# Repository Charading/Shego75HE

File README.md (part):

<h1 style="margin-bottom:0;">Shego75HE</h1>
<h4 style="margin-top:0;">Probably the first magnetic keyboard running QMK firmware.</h4>

> 📖 **[Read the latest update →](UPDATE.md)**

### Introduction&nbsp; 

I couldn't find a keyboard with the all of features that I wanted at all, so I resorted to building my own one. After testing a lot of keyboards, I wanted one that had a mix of all different features from multiple keyboards. This project has taken many, many, many months, starting from experimentaion and various mini protypes like the [Shego16](https://github.com/Charading/SHEGO16-QMK-Hall-Effect-Macropad).

### Design and Inspiration 💡
I think the exploded 75% layout is one of the best layouts but sadly it's not as aftermarket as the generic 60% layout so my only options for trying to find a board were scarce. For aesthetics, I went with Shego because my mind was blank and tbh, I just wanted a cool silkscreen too lol. 

I do love the **Ajazz AK820 Pro** and it's clean design, along with the added screen. I do wish it could run QMK/VIA firmware though. Another board I tested was the **GamaKay TK75HEV2** I wanted my board to be quite similar to both, but have everything I've ever wanted. 

Features I wanted

* Hall Sensors
* SOCD
* Rapid Trigger
* Volume Knob
* Ambient Lighting
* Screen
* North-facing RGB
* 75% Layout
* QMK/VIA Compatible
* Works with SignalRGB (per-key not that stupid one-zone nonsense)

#### Firmware 👨‍💻
I originally tried raw C, then riskable put me on Rust, but after creating a successful prototype, I had a revelation. the idea I had is to use normal QMK firmware since I was a little bit familiar with it, then heavily modify my clone of it to work with hall sensors. 

*I am still designing a drop in [module](https://github.com/Charading/qmk-hallscan) that can make anyone be able to use the logic for QMK. Project is ongoing*

Oh yeah, to make my life easier, and save my poor fingers from typing `qmk compile -kb shego75_v1 -km default` a million times, I developed a VS Code extension, a small one-click button that compiles QMK firmware. Find it [here](https://github.com/Charading/QMK-Compile-button-for-VS-Code).

The screen/ESP32 portion is written in C++ inside Arduino IDE.

###### The Sensors 🧲
After doing extensive research and testing with breadboards and Raspberry Pi Pico boards, I settled on using the RP2040 for my base MCU. I was going to use HC4067s, but I didn't really understand multiplexer cascading so after looking for a bit, I stumbled upon the ADG732 so I now use three of these, which means I do not need to use a MCP3208 external ADC *(my god, I recently was trying to get this to work using my sensor-to-matrix logic in QMK but couldn't for the life of me)* and I could use only 3 of the 4 analog pins.

###### How it works 🔎
Essentially, the bread and butter is that the firmware scans across three ADG732 muxes - *which I got really cheap for ~£2 on AliExpress*, and this 'injects' keypresses directly into the key matrix so that it works with VIA and key remapping also. 

On startup, the sensors calibrate with a baseline threshold and when the sensors deviate by a certain % amount, the keypress is registered. I even added hysteresis so I have some kind of rapid trigger.

Debugging keycodes enable printing to QMK Toolbox's HID Console

* `DEBUG_ADC`  - Prints ADC values
* `DEBUG_KEYS` - Prints on keypress events
* `DEBUG_RAW`  - Prints the raw VIA keycode on keypresses, i.e *0x67*

I believe it still prints keys and raw to the screen on a little popup text box too.

###### The Lighting 💡
For the lighting, I ket it simple, and just use SignalRGB,  but in the future I want to maybe add OpenRGB support as well and my own custom lighting section in my Electron app. I have made the [plugin](SignalRGB/SHEGO75.js).

It has full per-key north-facing rgb, a 10-led ambient strip and a 3-led status bar, there is also a 3-pin jst 1.25mm connector footprint in the corner for optional extending *(maybe for a future case, underglow?)*.

The SRGB plugin uses `LedGroups()` to create segments so it has three draggable windows to mess around with.

```javascript
export function LedGroups() {
	return [
		{ name: "Keys",    leds: vKeys },
		{ name: "Ambient", leds: vAmbientKeys },
		{ name: "Status", leds: vStatusKeys }
	];
}
```
 It is designed as one continuous strip though, on `GP17`, but there is a transistor pair on `GP23` which is controlled by the `LED_TOG` custom keycode and cuts power to the LEDs.

 When focused on the screen/layer 3 toggled, the status bar will turn blue.

 When debugging is enabled via `DEBUG_ADC`,`DEBUG_KEYS` or `DEBUG_RAW`, the ambient strip should marque orange.

###### The Screen 📺

Sadly, I couldn't figure out how to get SPI working to talk to the screen for GIF upload and playback via HID, so I approached it a different way.

I built an isolated ESP32 system using [my fork](/esp32_display) of a GIF player repo. I basically redid it to have a little menu and file system, and work a different way to the original. Instead of it automatically copying the GIF to flash and autoplaying, I can browse the SD card, choose which GIF to display, it copies it to SPIFFS, then plays. This way it persists even after power off. 

The screen is [this](https://www.aliexpress.com/item/1005004490846551.html) ST7735/GC9107 8-pin, 0.85", 128x128 IPS display.

To get the QMK firmware to communicate with the ESP32 system, I created custom VIA keycodes which send UART text strings and text commands such as `MENU_OPEN`, `MENU_UP`,`MENU_DOWN` and `MENU_SELECT` allow me to navigate and choose an animation.

4-stage PWM controlled backlight with `TFT_BRIGHTNESS_UP` and `TFT_BRIGHTNESS_DOWN`, via a [AO3401](https://www.aosmd.com/res/data_sheets/AO3401.pdf) transistor. 

I also made a a timer page, settings page, and hardcoded focus toggle which layer 3 + encoder press turns the rotation into menu navigation, and press is the select. 

In a small update, I added a I2C connection between the RP2040 and the ESP32 which I was thinking I could use for GIF passthrough and sending in the future but this is not implemented yet.

##### Firmware Issues
I want a way to use QMK's `raw_hid_receive` and `raw_hid_send` so I can have my own custom software that can change per-key actuation, I could implement DKS, upload GIFs to the SD card/directly to the screen and even manage the card's storage. 

I managed to create a small Electron app that can communicate with the board, but it's still in development.

I realised that SignalRGB consumes packets so I had to edit the `signalrgb.c` and `signalrgb.h` to not drop packets it doesn't recognise but I am still stuck because I can't get my app to even toggle GPIO23 which toggles power to the lighting. *I did manage to do it once but I reverted back because I have up, but this was before I changed the SRGB module. Now even with SRGB disabled, I still can't get my keyboard to toggle and I don't know what the issue is.*

I just want to be able to talk to my board over HID and then I can make it similar to all those Chinese OEM clone web apps and software, Wootings web app etc.

If anyone more knowledgable can assist or point me in the right direction that would be amazing!

####  Case ⚫

At the moment I am using a prototype case that I printed out of ELEGOO PLA-CF. I could technically get this machined by JLCCNC but I do not wish to increase spending at this time. I would rather wait and see if I can finalise my case beforehand to minimise revisions and metallic waste. 

I do wish I could find the smaller form factor ball catches that the **Lucky65** and many other newer boards use but I can't find somewhere that can machine them or find them aftermarket. So at the moment, it is a two piece design, designed similarily to the **CIDOO C75** and **TK75HEV2** but with the shaping somewhat resembling the **Tofu65** because I like the sharp edges. I really hate the designs that have such baby rounded edges like the **AK820 Pro MAX**.

It uses a daughterboard I designed, but maybe a future design I would want to to use pogo pin connectors like the **Lucky65 V3** but I would have to do some testing to see that the magnets do not interfer with normal keyboard function.

#### PCB 🟢

Just used KiCad, I kept having issues using the standalone ESP32-PICO-D4 and flashing it *(maybe it's because I was lazy and didn't implement a USB-UART chip)* so I did some looking and found the [TinyPICO Nano](https://github.com/tinypico). To help test with firmware and stuff, just to be safe and not rely on my firmware working with it just because it worked on the ESP32-WROOM-32 dev module, I designed [this adapter](https://github.com/Charading/flexypin_adapters_hw/tree/main/TinyPICO-NANO_flexypin) so interfacing and testing would be easier. The RP2040's `GP0` and `GP1` are broken out for UART0 debug.

### Future Updates/Roadmap 🚗
- I haven't really been focused on it much with this board, but I will be looking to implent tri-mode or at least 2.4GHz wireless with a dongle. For a coming soon, future project I want to design a drop in replacement pcb for the **Lucky65 V2** or **Lucky65 V3** running my custom magnetic QMK firmware because the cases are gorgeous and such a steal!

- Software/web app (most likely Electron powered)
- Implement GIF upload over USB 
- Motion design/3D design for promotional material, a small website as I would like to start a small store that sells keyboard stuff and keycaps.
- Full aluminium case needs to be machined 
- Maybe start a Kickstarter for a future keyboard project
- TMR keyboard maybe? 👀

>*I should say I came into this project with no prior knowledge of PCB design (proficient now), very miniscule coding knowledge (still a newbie though), and a small amount of CAD skill (which I am quite proficient at now I believe). My soldering skills are now extremely high as well* :).

### Special Thanks 🖤
- [**riskable**](https://github.com/riskable) for his online resources and availabilty to help me at various points in this project!

- **@hardbr** *(discord)* for helping me understand SignalRGB implentation

- [**Phils Lab**](https://github.com/pms67) for online resources *(Youtube)*

- **JLCPCB**

- **GitHub Copilot**, **ChatGPT**, **Claude**, **Gemini Pro** (actual life savers lmao)

## 24/12/2025 - Merry Christmas! 
## Huge Update:
I’ve got the software working and a completely new firmware stack built from the ground up. The app is **Electron-based** and (honestly) was mostly vibe-coded while I iterated on UX and device behavior. The firmware is also brand new—written specifically for this project and its multi‑MCU architecture.

A big part of this update is that we **moved fully away from QMK**. Instead of adapting QMK to fit the hardware and features, we started from scratch with a firmware designed around our exact data paths and performance goals: **USB HID on the RP2040**, a clean **UART link** to the ESP32 for UI/display responsibilities, and **SPI** for high-throughput TFT updates. Dropping QMK gave us tighter control over timing, memory, and feature integration, and removed the friction of forcing a general-purpose keyboard firmware into a system that’s doing more than “just key scanning.”

The project is currently in a private repo. If you want to follow along or chat about it, my Discord is **hyupdo**.

### App Preview

<h5 align="center">Keys</h5>

<h5 align="center">Lighting</h5>

<h5 align="center">Performance</h5>

<h5 align="center" style="margin-bottom: 0;">Screen</h5>

<div align="center" style="font-style: italic; line-height: 1;">
  <small>This feature is only available on the Shego75</small>
</div>

<div align="center" style="line-height: 2;">
  <small>Storage system using the SD ('Send to SD' yet to be implemented)</small>
</div>

### How to use:

#### Keys

Configure per-key actuation points, dead zones, and key assignments. The live visualization shows real-time magnetic sensor readings and key states. Customize individual key behavior with adjustable sensitivity ranges and enable anti-ghosting features. Export and import key profiles for quick configuration switching.

#### Lighting

In the **Lighting** tab, effects are driven using **SignalRGB**, which treats the keyboard like an addressable LED device and streams color data in real time. Once enabled, SignalRGB can take control of animations (audio-reactive, game integrations, ambient effects) and push them directly to the board so lighting stays perfectly in sync with the rest of your setup. You can still fine-tune how the device presents itself to SignalRGB—especially how LEDs are grouped and mapped—so the software knows what “keys” or regions it’s actually driving.

To change **zones**, use the zone controls to assign LEDs/keys into separate regions (for example: left half, right half, underglow, indicator cluster, or per-row groups). Each zone can be adjusted independently so you can apply different colors/effects per region, or scale brightness and effect intensity where you want it. After updating zone assignments, apply/save the configuration so the device reports the new layout and SignalRGB (or the app’s built-in effects) will target the updated zones correctly.

#### Performance

The **Performance** tab is a live “health dashboard” for the firmware and transport links, meant to answer one question quickly: *is the device keeping up in real time?* It aggregates timing, throughput, and workload counters so you can confirm that input scanning, lighting updates, and display/UI work are all completing within budget—especially when features are enabled simultaneously.

At a high level, the tab focuses on three areas:

1) **Frame / Loop Timing**
- Shows how long the main firmware loop (or “frame”) takes to run and how consistent it is over time.
- Look for **average**, **min/max**, and **spike** behavior. A stable system has tight variance; frequent spikes suggest something occasionally blocks (heavy rendering, long SPI transfers, or bursts of host traffic).
- If you see a “budget” or target interval, the goal is to keep the loop time comfortably below that target so there’s slack for bursts.

2) **Input Responsiveness**
- Tracks the cadence and workload of key scanning and event processing.
- Useful indicators include scan rate, event queue depth, and any dropped/late events.
- If responsiveness metrics degrade while other features are active, it’s a sign you should reduce background load (very high LED update rates, overly frequent display refresh, or excessive logging/telemetry).

3) **Transport + Subsystem Throughput (Host ⇄ RP2040 ⇄ ESP32 ⇄ TFT)**
- **USB/HID**: lets you see how often the host is sending commands and how quickly the device is responding. Excessive command rates can create overhead and jitter.
- **UART (RP2040 ⇄ ESP32)**: shows whether messages are flowing smoothly between MCUs. Watch for rising queue/backlog counters or retry/error counts—those often correlate with delayed UI updates.
- **SPI (ESP32 ⇄ TFT)**: large, frequent screen updates can dominate time. If you see display-related counters tied to spikes, consider lowering refresh frequency or reducing what’s being redrawn per update.

How to use it in practice:
- Start with everything “idle” and note the baseline loop time and stability.
- Enable one feature at a time (lighting effects, animations, screen updates, host polling) and watch what changes.
- If a metric provides “worst” or “spike” values, treat those as the most important—single long stalls are often more noticeable than a slightly higher average.
- Use the tab as a verification step after configuration changes: if you adjust lighting zones, increase effect complexity, or change display behavior, confirm the loop remains stable and queues don’t grow over time.

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
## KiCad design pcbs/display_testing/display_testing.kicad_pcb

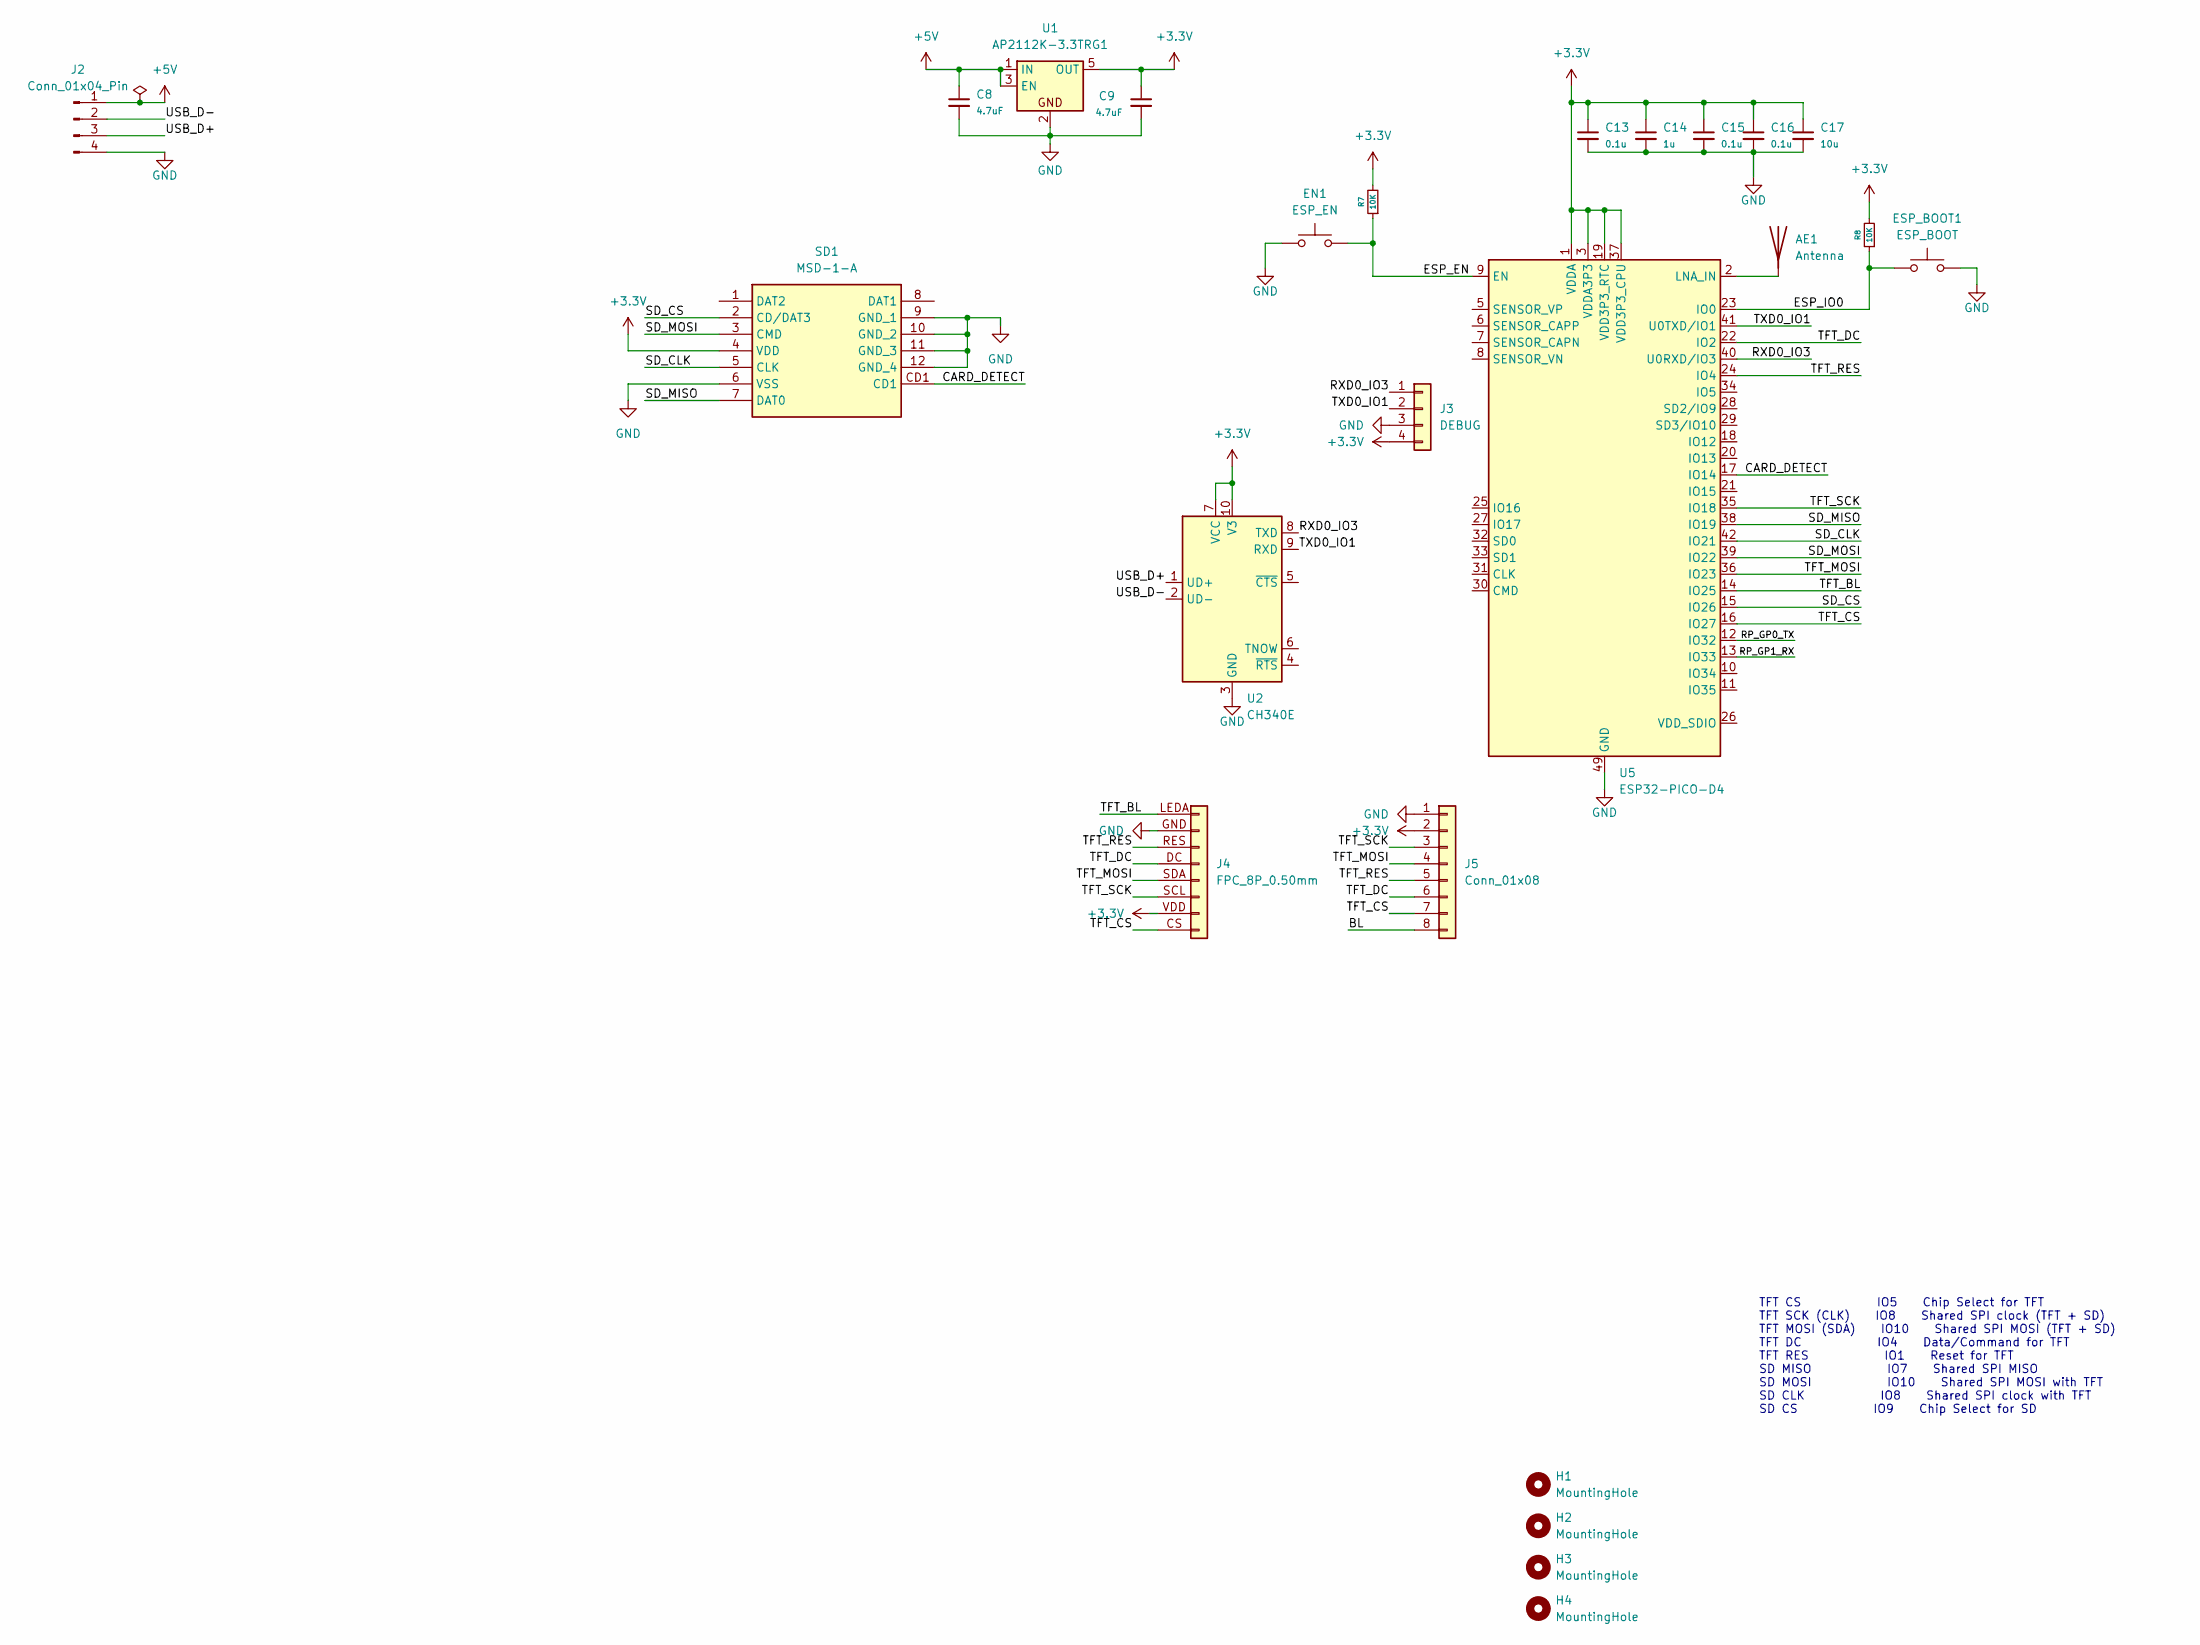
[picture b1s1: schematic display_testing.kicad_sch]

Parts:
AE1: Antenna; ESPRESSIF_ESP32_MIFA_2.4GHz_Right
C8, C9: 4.7uF; C_0805_2012Metric
C13, C15, C16: 0.1u; C_0603_1608Metric_Pad1.08x0.95mm_HandSolder
C14: 1u; C_0603_1608Metric_Pad1.08x0.95mm_HandSolder
C17: 10u; C_0603_1608Metric_Pad1.08x0.95mm_HandSolder
EN1: ESP_EN; SW_SPST_EVQP2_MiddlePushTravel_H2.5mm
ESP_BOOT1: ESP_BOOT; SW_SPST_EVQP2_MiddlePushTravel_H2.5mm
H1, H2, H3, H4: MountingHole; MountingHole_2.2mm_M2
J2: Conn_01x04_Pin
J3: DEBUG; SWD_Debug_PinHeader_1x04_P2.54mm; Part Number 1-0401FBV0T
J4: FPC_8P_0.50mm; TFT_FPC_8P_0.5mm
J5: Conn_01x08; PinHeader_1x08_P2.54mm_Vertical
R7, R8: 10K; R_0603
SD1: MSD-1-A; MSD1A; Manufacturer_Part_Number MSD-1-A; Mouser Part Number 179-MSD-1-A
U1: AP2112K-3.3TRG1; SOT-23-5
U2: CH340E; MSOP-10_3x3mm_P0.5mm
U5: ESP32-PICO-D4; QFN-48-1EP_7x7mm_P0.5mm_EP5.3x5.3mm

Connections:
+3.3V: C9.1, C13.1, C14.1, C15.1, C16.1, C17.1, J3.4, J4.VDD (Pin_7), J5.2, R7.2, R8.2, SD1.4 (VDD), U1.5 (OUT), U2.7 (VCC), U2.10 (V3), U5.1 (VDDA), U5.3 (VDDA3P3), U5.4 (VDDA3P3), U5.19 (VDD3P3_RTC), U5.37 (VDD3P3_CPU), U5.43 (VDDA), U5.46 (VDDA)
+5V: C8.1, J2.1, U1.1 (IN), U1.3 (EN)
/BL: J5.8
/CARD_DETECT: SD1.CD1, U5.17 (IO14)
/ESP_EN: EN1.2, R7.1, U5.9 (EN)
/ESP_IO0: ESP_BOOT1.1, R8.1, U5.23 (IO0)
/RP_GP0_TX: U5.12 (IO32)
/RP_GP1_RX: U5.13 (IO33)
/RXD0_IO3: J3.1, U2.8 (TXD), U5.40 (U0RXD/IO3)
/SD_CLK: SD1.5 (CLK), U5.42 (IO21)
/SD_CS: SD1.2 (CD/DAT3), U5.15 (IO26)
/SD_MISO: SD1.7 (DAT0), U5.38 (IO19)
/SD_MOSI: SD1.3 (CMD), U5.39 (IO22)
/TFT_BL: J4.LEDA (Pin_1), U5.14 (IO25)
/TFT_CS: J4.CS (Pin_8), J5.7, U5.16 (IO27)
/TFT_DC: J4.DC (Pin_4), J5.6, U5.22 (IO2)
/TFT_MOSI: J4.SDA (Pin_5), J5.4, U5.36 (IO23)
/TFT_RES: J4.RES (Pin_3), J5.5, U5.24 (IO4)
/TFT_SCK: J4.SCL (Pin_6), J5.3, U5.35 (IO18)
/TXD0_IO1: J3.2, U2.9 (RXD), U5.41 (U0TXD/IO1)
/USB_D+: J2.3, U2.1 (UD+)
/USB_D-: J2.2, U2.2 (UD-)
GND: C8.2, C9.2, C13.2, C14.2, C15.2, C16.2, C17.2, EN1.1, ESP_BOOT1.2, J2.4, J3.3, J4.GND (Pin_2), J5.1, SD1.6 (VSS), SD1.9 (GND_1), SD1.10 (GND_2), SD1.11 (GND_3), SD1.12 (GND_4), U1.2, U2.3 (GND), U5.49 (GND)
unnamed: AE1.1 (A), U5.2 (LNA_IN)

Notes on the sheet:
TFT CS IO5 Chip Select for TFT TFT SCK (CLK) IO8 Shared SPI clock (TFT + SD) TFT MOSI (SDA) IO10 Shared SPI MOSI (TFT + SD) TFT DC IO4 Data/Command for TFT TFT RES IO1 Reset for TFT SD MISO IO7 Shared SPI MISO SD MOSI IO10 Shared SPI MOSI with TFT SD CLK IO8 Shared SPI clock with TFT SD CS IO9 Chip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

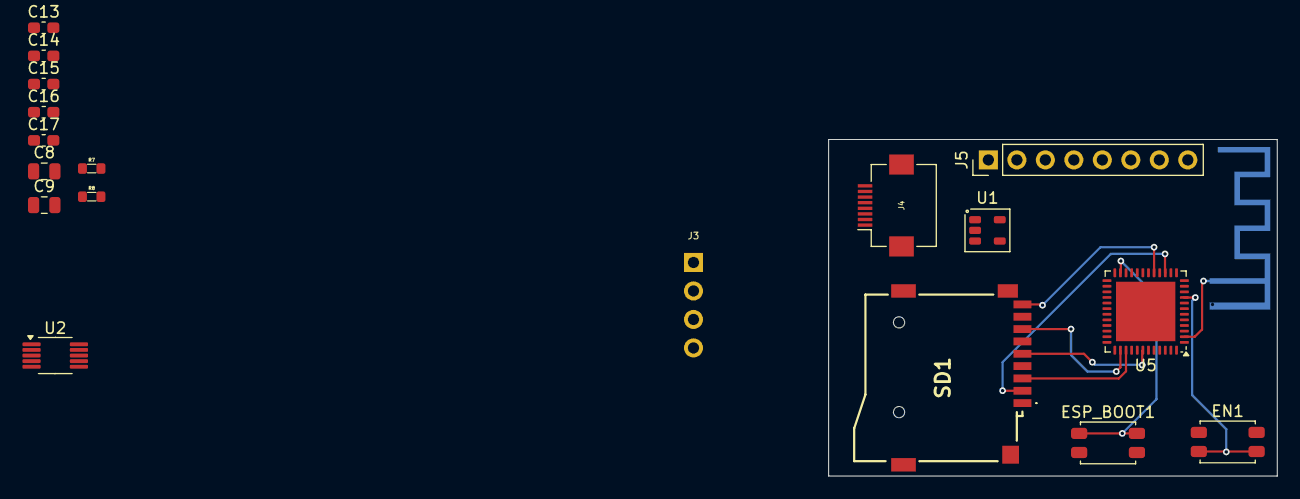
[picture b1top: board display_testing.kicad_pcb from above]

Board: 2 copper layers, 40.0 x 30.0 mm, 23 parts (1 on the bottom side), 19 nets.

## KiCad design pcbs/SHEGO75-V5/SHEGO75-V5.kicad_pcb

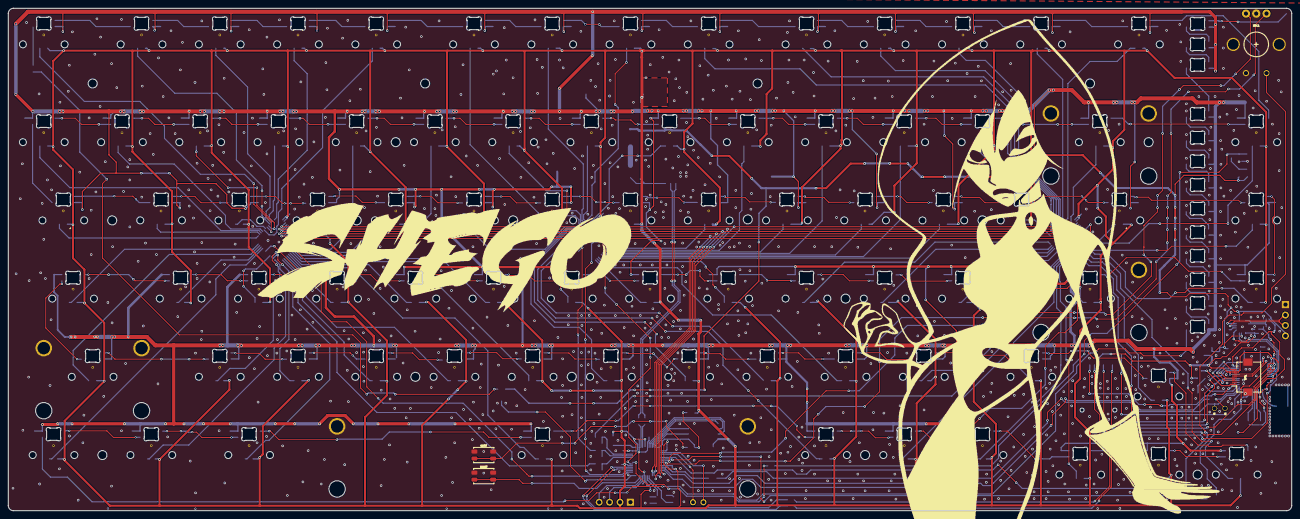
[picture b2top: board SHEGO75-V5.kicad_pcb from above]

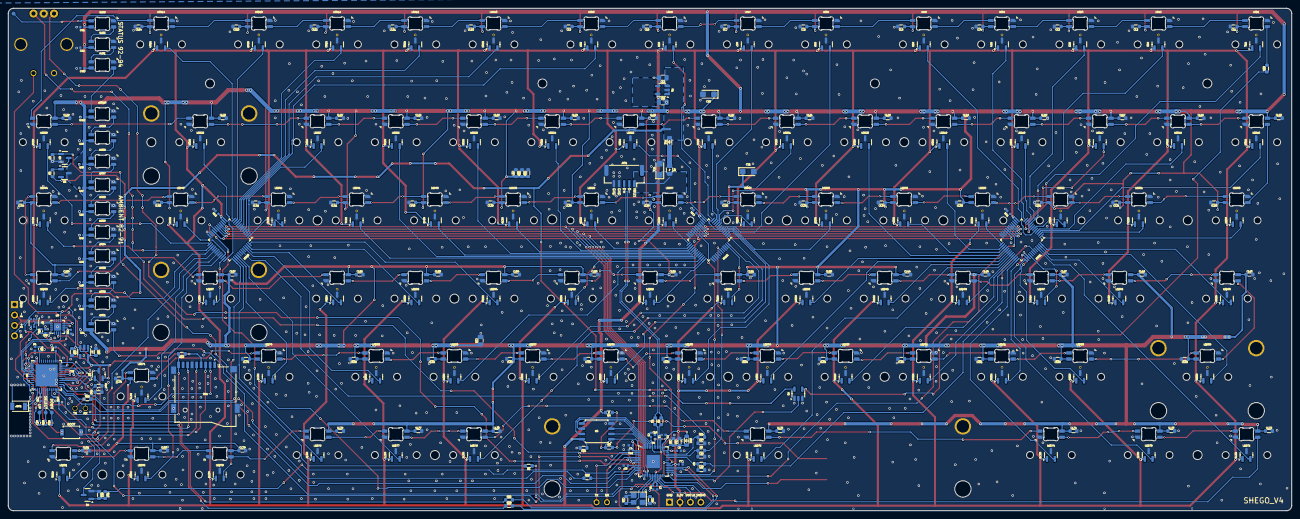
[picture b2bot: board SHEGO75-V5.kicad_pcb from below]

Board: 2 copper layers, 312.5 x 122.3 mm, 369 parts (362 on the bottom side), 265 nets.

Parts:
AMB1, AMB2, AMB3, AMB4, AMB5, AMB6, AMB7, AMB8, AMB9, AMB10: SK6812; LED_6028R
ANT1: ANT3216LL00R2400A; ANTC3216X135N
BOOT1: BOOTSEL; SW_SPST_EVQP2_MiddlePushTravel_H2.5mm
C1, C11: 1u; C_0402
C2, C3, C4, C5, C6, C7, C8, C9, C10, C28, C31, C32, C33, C35: 0.1u; C_0402
C12, C13: 10uF; C_0805
C14, C18, C19, C29, C30: 10uF; C_0603
C15: 0.1uF; C_0603
C16, C17: 0.1u; C_0603
C20: 47uF; C_0805
C21, C22: 47uF; CP_EIA-3216-12_Kemet-S
C23, C24: 30p; C_0603
C25, C26, C27: DNP; C_0603
C34: 1uF; C_0402
CA1, CA2, CA3, CA4, CA5, CA6, CA7, CA8, CA9, CA10: 0.1uF; C_0402
CG1, CG2, CG3: 0.1uF; C_0402
CL1, CL2, CL3, CL4, CL5, CL6, CL7, CL8, CL9, CL10, CL11, CL12, CL13, CL14, CL15, CL16, CL17, CL18, CL19, CL20, CL21, CL22, CL23, CL24, CL25, CL26, CL27, CL28, CL29, CL30, CL31, CL32, CL33, CL34, CL35, CL36, CL37, CL38, CL39, CL40, CL41, CL42, CL43, CL44, CL45, CL46, CL47, CL48, CL49, CL50, CL51, CL52, CL53, CL54, CL55, CL56, CL57, CL58, CL59, CL60, CL61, CL62, CL63, CL64, CL65, CL66, CL67, CL68, CL69, CL70, CL71, CL72, CL73, CL74, CL75, CL76, CL77, CL78, CL79, CL80, CL81: 0.1u; C_0603
D1: RED; LED_0402_1005Metric
ENC1: RotaryEncoder_Switch_MP; RotaryEncoder_Alps_EC11E_Vertical_H20mm_CircularMountingHol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
ESP_BOOT1: ESP_BOOT; SW_SPST_EVQP2
F1: 1.1A; Fuse_PPTC_0805
FB1, FB2: 600R; Ferrite_0805
GLO1, GLO2, GLO3: SK6812; LED_6028R
HE1, HE2, HE3, HE4, HE5, HE6, HE7, HE8, HE9, HE10, HE11, HE12, HE13, HE14, HE15, HE16, HE17, HE18, HE19, HE20, HE21, HE22, HE23, HE24, HE25, HE26, HE27, HE29, HE31, HE32, HE33, HE34, HE35, HE36, HE37, HE38, HE39, HE40, HE41, HE42, HE44, HE46, HE47, HE48, HE49, HE50, HE51, HE52, HE53, HE54, HE55, HE56, HE58, HE60, HE61, HE62, HE63, HE64, HE65, HE66, HE67, HE68, HE69, HE71, HE76, HE77, HE78, HE79, HE80, HE81: 49E; SW_MX_HE_90deg_1u_Rules
HE28: 49E; SW_MX_HE_90deg_2.00u_Rules
HE30, HE43: 49E; SW_MX_HE_90deg_1.5u_Rules
HE45, HE70: 49E; SW_MX_HE_90deg_1.75u_Rules
HE57, HE59: 49E; SW_MX_HE_90deg_2.25u_Rules
HE72, HE73, HE74: 49E; SW_MX_HE_90deg_1.25u_Rules
HE75: 49E; SW_MX_HE_90deg_6.25u_Rules
JST1: MOMMY; JST_GH_SM05B-GHS-TB_1x05-1MP_P1.25mm_Horizontal
LED1, LED2, LED3, LED4, LED5, LED6, LED7, LED8, LED9, LED10, LED11, LED12, LED13, LED14, LED15, LED16, LED17, LED18, LED19, LED20, LED21, LED22, LED23, LED24, LED25, LED26, LED27, LED28, LED29, LED30, LED31, LED32, LED33, LED34, LED35, LED36, LED37, LED38, LED39, LED40, LED41, LED42, LED43, LED44, LED45, LED46, LED47, LED48, LED49, LED50, LED51, LED52, LED53, LED54, LED55, LED56, LED57, LED58, LED59, LED60, LED61, LED62, LED63, LED64, LED65, LED66, LED67, LED68, LED69, LED70, LED71, LED72, LED73, LED74, LED75, LED76, LED77, LED78, LED79, LED80, LED81: SK6812; LED_6028R
MC1, MC2, MC3: 0.1uF; C_0402
MUX1, MUX2, MUX3: ADG732BSUZ; TQFP-48_7x7mm_P0.5mm
Q1, Q3: AO3401A; SOT-23
Q2, Q4: BSS138; SOT-23
Q7: UMH3N; SOT-363_SC-70-6
R1, R2: 27; R_0603
R3: 1k; R_0603
R4: DNP; R_0603
R5, R6, R12, R14: 100K; R_0603
R7, R15: 1M; R_0603
R8, R9, R10, R11: 100; R_0603
R13: 10k; R_0603
R16: 1K; R_0402
R17, R18, R19: 12K; R_0402
R20, R21: 47; R_0603
R22, R23: 0; R_0603
R24: 330; R_0603
R25: 10K; R_0402
RES1: RESET; SW_SPST_EVQP2_MiddlePushTravel_H2.5mm
SD1: MSD-1-A; MSD1A
SWD1: DEBUG; SWD_Debug_PinHeader_1x04_P2.54mm
SWD2: ESP_FLASH; SWD_Debug_PinHeader_1x04_P2.54mm
TFT1: FPC_8P; TFT_FPC_8P_0.5mm
TP1: UP; TestPoint_Pad_04
TP2: DOWN; TestPoint_Pad_04
TP3: SELECT; TestPoint_Pad_04
TP4: EXP; TestPoint_Pad_04
U1, U7: AP2112K-3.3; SOT-23-5
U2: SN74LV1T125DBV; SOT-23-5
U3: W25Q128JVS; SOIC-8_5.3x5.3mm_P1.27mm
U4: RP2040; QFN-56-1EP_7x7mm_P0.4mm_EP3.2x3.2mm
U6: ESP32-PICO-D4; QFN-48-1EP_7x7mm_P0.5mm_EP5.3x5.3mm
U8: CH343P; WCH_QFN-16-1EP_3x3mm_P0.5mm_EP1.8x1.8mm
UART1, UART2: RP_UART; UART_PinHeader_1x02_P2.54mm
VC1: 47uF; CP_EIA-3216-12_Kemet-S
Y1: 12MHz; Crystal_SMD_3225-4Pin_3.2x2.5mm

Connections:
3V_RGB: U2.2 (A), U4.28 (GPIO17)
5V_RGB_OUT: R24.1, U2.4 (Y)
+1V1: C1.1, C2.1, C3.1, U4.23 (DVDD), U4.45 (VREG_VOUT), U4.50 (DVDD)
+3V3: C4.1, C5.1, C6.1, C7.1, C8.1, C9.1, C10.1, C11.1, C13.1, C16.1, FB2.1, HE1.1 (VCC), HE2.1 (VCC), HE3.1 (VCC), HE4.1 (VCC), HE5.1 (VCC), HE6.1 (VCC), HE7.1 (VCC), HE8.1 (VCC), HE9.1 (VCC), HE10.1 (VCC), HE11.1 (VCC), HE12.1 (VCC), HE13.1 (VCC), HE14.1 (VCC), HE15.1 (VCC), HE16.1 (VCC), HE17.1 (VCC), HE18.1 (VCC), HE19.1 (VCC), HE20.1 (VCC), HE21.1 (VCC), HE22.1 (VCC), HE23.1 (VCC), HE24.1 (VCC), HE25.1 (VCC), HE26.1 (VCC), HE27.1 (VCC), HE28.1 (VCC), HE29.1 (VCC), HE30.1 (VCC), HE31.1 (VCC), HE32.1 (VCC), HE33.1 (VCC), HE34.1 (VCC), HE35.1 (VCC), HE36.1 (VCC), HE37.1 (VCC), HE38.1 (VCC), HE39.1 (VCC), HE40.1 (VCC), HE41.1 (VCC), HE42.1 (VCC), HE43.1 (VCC), HE44.1 (VCC), HE45.1 (VCC), HE46.1 (VCC), HE47.1 (VCC), HE48.1 (VCC), HE49.1 (VCC), HE50.1 (VCC), HE51.1 (VCC), HE52.1 (VCC), HE53.1 (VCC), HE54.1 (VCC), HE55.1 (VCC), HE56.1 (VCC), HE57.1 (VCC), HE58.1 (VCC), HE59.1 (VCC), HE60.1 (VCC), HE61.1 (VCC), HE62.1 (VCC), HE63.1 (VCC), HE64.1 (VCC), HE65.1 (VCC), HE66.1 (VCC), HE67.1 (VCC), HE68.1 (VCC), HE69.1 (VCC), HE70.1 (VCC), HE71.1 (VCC), HE72.1 (VCC), HE73.1 (VCC), HE74.1 (VCC), HE75.1 (VCC), HE76.1 (VCC), HE77.1 (VCC), HE78.1 (VCC), HE79.1 (VCC), HE80.1 (VCC), HE81.1 (VCC), MC1.1, MC2.1, MC3.1, MUX1.13 (VDD), MUX1.14 (VDD), MUX2.13 (VDD), MUX2.14 (VDD), MUX3.13 (VDD), MUX3.14 (VDD), R4.2, SWD1.2, U1.5 (VOUT), U3.8 (VCC), U4.1 (IOVDD), U4.10 (IOVDD), U4.22 (IOVDD), U4.33 (IOVDD), U4.42 (IOVDD), U4.44 (VREG_IN), U4.48 (USB_VDD), U4.49 (IOVDD)
+3V3A: C14.1, C15.1, FB2.2, U4.43 (ADC_AVDD)
+3V3_ESP: C30.1, C32.1, C33.1, C35.1, Q3.2 (S), R13.2, R17.1, R18.1, R19.1, R25.1, SD1.4 (VDD), TFT1.VDD (Pin_7), U6.1 (VDDA), U6.3 (VDDA3P3), U6.4 (VDDA3P3), U6.19 (VDD3P3_RTC), U6.37 (VDD3P3_CPU), U6.43 (VDDA), U6.46 (VDDA), U7.5 (VOUT), U8.1 (VIO)
+5V: C12.1, C29.1, FB1.2, Q1.2 (S), R5.2, SWD2.1, U1.1 (VIN), U1.3 (EN), U2.5 (VCC), U7.1 (VIN), U7.3 (EN), U8.3 (VDD5), U8.9 (VBUS)
+5V_LED: AMB1.1 (VDD), AMB2.1 (VDD), AMB3.1 (VDD), AMB4.1 (VDD), AMB5.1 (VDD), AMB6.1 (VDD), AMB7.1 (VDD), AMB8.1 (VDD), AMB9.1 (VDD), AMB10.1 (VDD), C17.1, C18.1, C19.1, C20.1, C21.1, C22.1, CA1.1, CA2.1, CA3.1, CA4.1, CA5.1, CA6.1, CA7.1, CA8.1, CA9.1, CA10.1, CG1.1, CG2.1, CG3.1, CL1.1, CL2.1, CL3.1, CL4.1, CL5.1, CL6.1, CL7.1, CL8.1, CL9.1, CL10.1, CL11.1, CL12.1, CL13.1, CL14.1, CL15.1, CL16.1, CL17.1, CL18.1, CL19.1, CL20.1, CL21.1, CL22.1, CL23.1, CL24.1, CL25.1, CL26.1, CL27.1, CL28.1, CL29.1, CL30.1, CL31.1, CL32.1, CL33.1, CL34.1, CL35.1, CL36.1, CL37.1, CL38.1, CL39.1, CL40.1, CL41.1, CL42.1, CL43.1, CL44.1, CL45.1, CL46.1, CL47.1, CL48.1, CL49.1, CL50.1, CL51.1, CL52.1, CL53.1, CL54.1, CL55.1, CL56.1, CL57.1, CL58.1, CL59.1, CL60.1, CL61.1, CL62.1, CL63.1, CL64.1, CL65.1, CL66.1, CL67.1, CL68.1, CL69.1, CL70.1, CL71.1, CL72.1, CL73.1, CL74.1, CL75.1, CL76.1, CL77.1, CL78.1, CL79.1, CL80.1, CL81.1, GLO1.1 (VDD), GLO2.1 (VDD), GLO3.1 (VDD), LED1.1 (VDD), LED2.1 (VDD), LED3.1 (VDD), LED4.1 (VDD), LED5.1 (VDD), LED6.1 (VDD), LED7.1 (VDD), LED8.1 (VDD), LED9.1 (VDD), LED10.1 (VDD), LED11.1 (VDD), LED12.1 (VDD), LED13.1 (VDD), LED14.1 (VDD), LED15.1 (VDD), LED16.1 (VDD), LED17.1 (VDD), LED18.1 (VDD), LED19.1 (VDD), LED20.1 (VDD), LED21.1 (VDD), LED22.1 (VDD), LED23.1 (VDD), LED24.1 (VDD), LED25.1 (VDD), LED26.1 (VDD), LED27.1 (VDD), LED28.1 (VDD), LED29.1 (VDD), LED30.1 (VDD), LED31.1 (VDD), LED32.1 (VDD), LED33.1 (VDD), LED34.1 (VDD), LED35.1 (VDD), LED36.1 (VDD), LED37.1 (VDD), LED38.1 (VDD), LED39.1 (VDD), LED40.1 (VDD), LED41.1 (VDD), LED42.1 (VDD), LED43.1 (VDD), LED44.1 (VDD), LED45.1 (VDD), LED46.1 (VDD), LED47.1 (VDD), LED48.1 (VDD), LED49.1 (VDD), LED50.1 (VDD), LED51.1 (VDD), LED52.1 (VDD), LED53.1 (VDD), LED54.1 (VDD), LED55.1 (VDD), LED56.1 (VDD), LED57.1 (VDD), LED58.1 (VDD), LED59.1 (VDD), LED60.1 (VDD), LED61.1 (VDD), LED62.1 (VDD), LED63.1 (VDD), LED64.1 (VDD), LED65.1 (VDD), LED66.1 (VDD), LED67.1 (VDD), LED68.1 (VDD), LED69.1 (VDD), LED70.1 (VDD), LED71.1 (VDD), LED72.1 (VDD), LED73.1 (VDD), LED74.1 (VDD), LED75.1 (VDD), LED76.1 (VDD), LED77.1 (VDD), LED78.1 (VDD), LED79.1 (VDD), LED80.1 (VDD), LED81.1 (VDD), Q1.3 (D)
/50ohm: ANT1.1 (FEED), U6.2 (LNA_IN)
/BL_GATE: Q3.1 (G), R10.2, R12.2
/CARD_DETECT: R13.1, SD1.CD1, U6.11 (IO35)
/ESP_D+: SWD2.2, U8.7 (UD+)
/ESP_D-: SWD2.3, U8.8 (UD-)
/ESP_EN: C34.1, Q4.3 (D), Q7.6 (C1), R25.2, U6.9 (EN)
/ESP_IO0: ESP_BOOT1.1, Q7.3 (C2), U6.23 (IO0)
/ESP_RST: R14.2, U4.5 (GPIO3)
/FB1: F1.2, FB1.1
/GP0_TX: U4.2 (GPIO0), UART1.1
/GP1_RX: U4.3 (GPIO1), UART1.2
/GP8_TX: R20.2, U4.11 (GPIO8)
/GP9_RX: R21.2, U4.12 (GPIO9)
/GP20_SDA: R22.2, U4.31 (GPIO20)
/GP21_SCL: R23.2, U4.32 (GPIO21)
/GP23_LED_EN: R6.1, U4.35 (GPIO23)
/GPIO26: C25.1, R8.1, U4.38 (GPIO26_ADC0)
/GPIO27: C26.1, R9.1, U4.39 (GPIO27_ADC1)
/GPIO28: C27.1, R11.1, U4.40 (GPIO28_ADC2)
/IO13_ESP_SDA: R22.1, U6.17 (IO14)
/IO14_ESP_SCL: R23.1, U6.21 (IO15)
/IO25_TFT_BL: R10.1, U6.14 (IO25)
/IO32_ESP_RX: R20.1, U6.12 (IO32), UART2.1
/IO33_ESP_TX: R21.1, U6.13 (IO33), UART2.2
/IO36: R17.2, TP1.1, U6.5 (SENSOR_VP)
/IO37: R18.2, TP2.1, U6.6 (SENSOR_CAPP)
/IO38: R19.2, TP3.1, U6.7 (SENSOR_CAPN)
/LED_GATE: Q2.1 (G), R6.2, R7.2
/MCU_D+: R1.2, U4.47 (USB_DP)
/MCU_D-: R2.1, U4.46 (USB_DM)
/N_DRAIN_5V: Q1.1 (G), Q2.3 (D), R5.1
/QSPI_SCLK: U3.6 (CLK), U4.52 (QSPI_SCLK)
/QSPI_SD0: U3.5 (DI/IO_{0}), U4.53 (QSPI_SD0)
/QSPI_SD1: U3.2 (DO/IO_{1}), U4.55 (QSPI_SD1)
/QSPI_SD2: U3.3 (~WP/IO_{2}), U4.54 (QSPI_SD2)
/QSPI_SD3: U3.7 (~HOLD/~RESET/IO_{3}), U4.51 (QSPI_SD3)
/QSPI_SS: R3.1, R4.1, U3.1 (~CS), U4.56 (QSPI_SS)
/RES_GATE: Q4.1 (G), R14.1, R15.2
/RUN: RES1.2, U4.26 (RUN)
/RXD0_IO3: U6.40 (U0RXD/IO3), U8.4 (TXD)
/SD_CLK: SD1.5 (CLK), U6.42 (IO21)
/SD_CS: SD1.2 (CD/DAT3), U6.15 (IO26)
/SD_MISO: SD1.7 (DAT0), U6.38 (IO19)
/SD_MOSI: SD1.3 (CMD), U6.39 (IO22)
/SWCLK: SWD1.3, U4.24 (SWCLK)
/SWDIO: SWD1.4, U4.25 (SWD)
/TFT_BL: Q3.3 (D), TFT1.LEDA (Pin_1)
/TFT_CS: TFT1.CS (Pin_8), U6.16 (IO27)
/TFT_DC: TFT1.DC (Pin_4), U6.22 (IO2)
/TFT_MOSI: TFT1.SDA (Pin_5), U6.36 (IO23)
/TFT_RES: TFT1.RES (Pin_3), U6.24 (IO4)
/TFT_SCK: TFT1.SCL (Pin_6), U6.35 (IO18)
/TXD0_IO1: U6.41 (U0TXD/IO1), U8.5 (RXD)
/USB_BOOT: BOOT1.2, R3.2
/XIN: C23.2, U4.20 (XIN), Y1.3
/XOUT: C24.2, U4.21 (XOUT), Y1.1
/leds/LED_EXP: GLO3.2 (DOUT), TP4.1
/leds/LED_IN: LED1.3 (DIN), R24.2
/sensors/HE1_Esc: HE1.2 (VOUT), MUX1.7 (S6)
/sensors/HE2_F1: HE2.2 (VOUT), MUX1.9 (S4)
/sensors/HE3_F2: HE3.2 (VOUT), MUX1.10 (S3)
/sensors/HE4_F3: HE4.2 (VOUT), MUX1.12 (S1)
/sensors/HE5_F4: HE5.2 (VOUT), MUX1.5 (S8)
/sensors/HE6_F5: HE6.2 (VOUT), MUX2.5 (S8)
/sensors/HE7_F6: HE7.2 (VOUT), MUX2.10 (S3)
/sensors/HE8_F7: HE8.2 (VOUT), MUX2.12 (S1)
/sensors/HE9_F8: HE9.2 (VOUT), MUX3.5 (S8)
/sensors/HE10_F9: HE10.2 (VOUT), MUX3.7 (S6)
/sensors/HE11_F10: HE11.2 (VOUT), MUX3.9 (S4)
/sensors/HE12_F11: HE12.2 (VOUT), MUX3.10 (S3)
/sensors/HE13_F12: HE13.2 (VOUT), MUX3.11 (S2)
/sensors/HE14_Del: HE14.2 (VOUT), MUX3.12 (S1)
/sensors/HE15_Grave: HE15.2 (VOUT), MUX1.3 (S10)
/sensors/HE16_1: HE16.2 (VOUT), MUX1.4 (S9)
/sensors/HE17_2: HE17.2 (VOUT), MUX1.8 (S5)
/sensors/HE18_3: HE18.2 (VOUT), MUX1.11 (S2)
/sensors/HE19_4: HE19.2 (VOUT), MUX1.26 (S18)
/sensors/HE20_5: HE20.2 (VOUT), MUX1.28 (S20)
/sensors/HE21_6: HE21.2 (VOUT), MUX2.9 (S4)
/sensors/HE22_7: HE22.2 (VOUT), MUX2.11 (S2)
/sensors/HE23_8: HE23.2 (VOUT), MUX2.7 (S6)
/sensors/HE24_9: HE24.2 (VOUT), MUX2.27 (S19)
/sensors/HE25_0: HE25.2 (VOUT), MUX2.29 (S21)
/sensors/HE26_Minus: HE26.2 (VOUT), MUX2.31 (S23)
/sensors/HE27_Equals: HE27.2 (VOUT), MUX3.3 (S10)
/sensors/HE28_Backspace: HE28.2 (VOUT), MUX3.36 (S28)
/sensors/HE29_Home: HE29.2 (VOUT), MUX3.25 (S17)
/sensors/HE30_Tab: HE30.2 (VOUT), MUX1.1 (S12)
/sensors/HE31_Q: HE31.2 (VOUT), MUX1.2 (S11)
/sensors/HE32_W: HE32.2 (VOUT), MUX1.6 (S7)
/sensors/HE33_E: HE33.2 (VOUT), MUX1.25 (S17)
/sensors/HE34_R: HE34.2 (VOUT), MUX1.27 (S19)
/sensors/HE35_T: HE35.2 (VOUT), MUX2.4 (S9)
/sensors/HE36_Y: HE36.2 (VOUT), MUX2.8 (S5)
/sensors/HE37_U: HE37.2 (VOUT), MUX2.25 (S17)
/sensors/HE38_I: HE38.2 (VOUT), MUX2.26 (S18)
/sensors/HE39_O: HE39.2 (VOUT), MUX2.28 (S20)
/sensors/HE40_P: HE40.2 (VOUT), MUX2.30 (S22)
/sensors/HE41_LeftBracket: HE41.2 (VOUT), MUX2.32 (S24)
/sensors/HE42_RightBracket: HE42.2 (VOUT), MUX3.1 (S12)
/sensors/HE43_Backslash: HE43.2 (VOUT), MUX3.34 (S26)
/sensors/HE44_PgUp: HE44.2 (VOUT), MUX3.26 (S18)
/sensors/HE45_CapsLock: HE45.2 (VOUT), MUX1.48 (S13)
/sensors/HE46_A: HE46.2 (VOUT), MUX1.46 (S15)
/sensors/HE47_S: HE47.2 (VOUT), MUX1.40 (S32)
/sensors/HE48_D: HE48.2 (VOUT), MUX1.33 (S25)
/sensors/HE49_F: HE49.2 (VOUT), MUX1.31 (S23)
/sensors/HE50_G: HE50.2 (VOUT), MUX1.29 (S21)
/sensors/HE51_H: HE51.2 (VOUT), MUX2.47 (S14)
/sensors/HE52_J: HE52.2 (VOUT), MUX2.36 (S28)
/sensors/HE53_K: HE53.2 (VOUT), MUX2.34 (S26)
/sensors/HE54_L: HE54.2 (VOUT), MUX3.48 (S13)
/sensors/HE55_Semicolon: HE55.2 (VOUT), MUX3.47 (S14)
/sensors/HE56_Quote: HE56.2 (VOUT), MUX3.46 (S15)
/sensors/HE57_Enter: HE57.2 (VOUT), MUX3.35 (S27)
/sensors/HE58_PgDn: HE58.2 (VOUT), MUX3.27 (S19)
/sensors/HE59_ShiftL: HE59.2 (VOUT), MUX1.47 (S14)
/sensors/HE60_Z: HE60.2 (VOUT), MUX1.39 (S31)
/sensors/HE61_X: HE61.2 (VOUT), MUX1.38 (S30)
/sensors/HE62_C: HE62.2 (VOUT), MUX1.35 (S27)
/sensors/HE63_V: HE63.2 (VOUT), MUX1.34 (S26)
/sensors/HE64_B: HE64.2 (VOUT), MUX1.30 (S22)
/sensors/HE65_N: HE65.2 (VOUT), MUX2.3 (S10)
/sensors/HE66_M: HE66.2 (VOUT), MUX2.2 (S11)
/sensors/HE67_Comma: HE67.2 (VOUT), MUX2.48 (S13)
/sensors/HE68_Period: HE68.2 (VOUT), MUX2.35 (S27)
/sensors/HE69_Slash: HE69.2 (VOUT), MUX3.45 (S16)
/sensors/HE70_ShiftR: HE70.2 (VOUT), MUX3.39 (S31)
/sensors/HE71_ArrowUp: HE71.2 (VOUT), MUX3.31 (S23)
/sensors/HE72_CtrlL: HE72.2 (VOUT), MUX1.45 (S16)
/sensors/HE73_Win: HE73.2 (VOUT), MUX1.37 (S29)
/sensors/HE74_AltL: HE74.2 (VOUT), MUX1.36 (S28)
/sensors/HE75_Space: HE75.2 (VOUT), MUX1.32 (S24)
/sensors/HE76_AltR: HE76.2 (VOUT), MUX2.1 (S12)
/sensors/HE77_Fn: HE77.2 (VOUT), MUX3.40 (S32)
/sensors/HE78_CtrlR: HE78.2 (VOUT), MUX3.38 (S30)
/sensors/HE79_ArrowLeft: HE79.2 (VOUT), MUX3.37 (S29)
/sensors/HE80_ArrowDown: HE80.2 (VOUT), MUX3.33 (S25)
/sensors/HE81_ArrowRight: HE81.2 (VOUT), MUX3.29 (S21)
AMB_IN: AMB1.3 (DIN), LED72.2 (DOUT)
D+: JST1.3, R1.1
D-: JST1.2, R2.2
DTR: Q7.2 (B1), U8.12 (~DTR)
ENC_A: ENC1.A, U4.7 (GPIO5)
ENC_B: ENC1.B, U4.8 (GPIO6)
ENC_SW: ENC1.S1, U4.6 (GPIO4)
GND: AMB1.4 (VSS), AMB2.4 (VSS), AMB3.4 (VSS), AMB4.4 (VSS), AMB5.4 (VSS), AMB6.4 (VSS), AMB7.4 (VSS), AMB8.4 (VSS), AMB9.4 (VSS), AMB10.4 (VSS), ANT1.2 (NC), BOOT1.1, C1.2, C2.2, C3.2, C4.2, C5.2, C6.2, C7.2, C8.2, C9.2, C10.2, C11.2, C12.2, C13.2, C14.2, C15.2, C16.2, C17.2, C18.2, C19.2, C20.2, C21.2, C22.2, C23.1, C24.1, C25.2, C26.2, C27.2, C28.1, C29.2, C30.2, C31.2, C32.2, C33.2, C34.2, C35.2, CA1.2, CA2.2, CA3.2, CA4.2, CA5.2, CA6.2, CA7.2, CA8.2, CA9.2, CA10.2, CG1.2, CG2.2, CG3.2, CL1.2, CL2.2, CL3.2, CL4.2, CL5.2, CL6.2, CL7.2, CL8.2, CL9.2, CL10.2, CL11.2, CL12.2, CL13.2, CL14.2, CL15.2, CL16.2, CL17.2, CL18.2, CL19.2, CL20.2, CL21.2, CL22.2, CL23.2, CL24.2, CL25.2, CL26.2, CL27.2, CL28.2, CL29.2, CL30.2, CL31.2, CL32.2, CL33.2, CL34.2, CL35.2, CL36.2, CL37.2, CL38.2, CL39.2, CL40.2, CL41.2, CL42.2, CL43.2, CL44.2, CL45.2, CL46.2, CL47.2, CL48.2, CL49.2, CL50.2, CL51.2, CL52.2, CL53.2, CL54.2, CL55.2, CL56.2, CL57.2, CL58.2, CL59.2, CL60.2, CL61.2, CL62.2, CL63.2, CL64.2, CL65.2, CL66.2, CL67.2, CL68.2, CL69.2, CL70.2, CL71.2, CL72.2, CL73.2, CL74.2, CL75.2, CL76.2, CL77.2, CL78.2, CL79.2, CL80.2, CL81.2, D1.1 (K), ENC1.C, ENC1.MP, ENC1.S2, ESP_BOOT1.2, GLO1.4 (VSS), GLO2.4 (VSS), GLO3.4 (VSS), HE1.3 (GND), HE2.3 (GND), HE3.3 (GND), HE4.3 (GND), HE5.3 (GND), HE6.3 (GND), HE7.3 (GND), HE8.3 (GND), HE9.3 (GND), HE10.3 (GND), HE11.3 (GND), HE12.3 (GND), HE13.3 (GND), HE14.3 (GND), HE15.3 (GND), HE16.3 (GND), HE17.3 (GND), HE18.3 (GND), HE19.3 (GND), HE20.3 (GND), HE21.3 (GND), HE22.3 (GND), HE23.3 (GND), HE24.3 (GND), HE25.3 (GND), HE26.3 (GND), HE27.3 (GND), HE28.3 (GND), HE29.3 (GND), HE30.3 (GND), HE31.3 (GND), HE32.3 (GND), HE33.3 (GND), HE34.3 (GND), HE35.3 (GND), HE36.3 (GND), HE37.3 (GND), HE38.3 (GND), HE39.3 (GND), HE40.3 (GND), HE41.3 (GND), HE42.3 (GND), HE43.3 (GND), HE44.3 (GND), HE45.3 (GND), HE46.3 (GND), HE47.3 (GND), HE48.3 (GND)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
MUX1: MUX1.43 (D), R8.2
MUX2: MUX2.43 (D), R9.2
MUX3: MUX3.43 (D), R11.2
MUX_A0: MUX1.15 (A0), MUX2.15 (A0), MUX3.15 (A0), U4.14 (GPIO11)
MUX_A1: MUX1.16 (A1), MUX2.16 (A1), MUX3.16 (A1), U4.15 (GPIO12)
MUX_A2: MUX1.17 (A2), MUX2.17 (A2), MUX3.17 (A2), U4.16 (GPIO13)
MUX_A3: MUX1.18 (A3), MUX2.18 (A3), MUX3.18 (A3), U4.17 (GPIO14)
MUX_A4: MUX1.19 (A4), MUX2.19 (A4), MUX3.19 (A4), U4.18 (GPIO15)
MUX_CS1: MUX1.20 (~CS), U4.29 (GPIO18)
MUX_CS2: MUX2.20 (~CS), U4.30 (GPIO19)
MUX_CS3: MUX3.20 (~CS), U4.13 (GPIO10)
MUX_WR: MUX1.21 (~WR), MUX2.21 (~WR), MUX3.21 (~WR), U4.34 (GPIO22)
unnamed: AMB1.2 (DOUT), AMB2.3 (DIN)
unnamed: AMB2.2 (DOUT), AMB3.3 (DIN)
unnamed: AMB3.2 (DOUT), AMB4.3 (DIN)
unnamed: AMB4.2 (DOUT), AMB5.3 (DIN)
unnamed: AMB5.2 (DOUT), AMB6.3 (DIN)
unnamed: AMB6.2 (DOUT), AMB7.3 (DIN)
unnamed: AMB7.2 (DOUT), AMB8.3 (DIN)
unnamed: AMB8.2 (DOUT), AMB9.3 (DIN)
unnamed: AMB9.2 (DOUT), AMB10.3 (DIN)
unnamed: D1.2 (A), R16.1
unnamed: GLO1.2 (DOUT), GLO2.3 (DIN)
unnamed: GLO2.2 (DOUT), GLO3.3 (DIN)
unnamed: LED1.2 (DOUT), LED2.3 (DIN)
unnamed: LED2.2 (DOUT), LED3.3 (DIN)
unnamed: LED3.2 (DOUT), LED4.3 (DIN)
unnamed: LED4.2 (DOUT), LED5.3 (DIN)
unnamed: LED5.2 (DOUT), LED6.3 (DIN)
unnamed: LED6.2 (DOUT), LED7.3 (DIN)
unnamed: LED7.2 (DOUT), LED8.3 (DIN)
unnamed: LED8.2 (DOUT), LED9.3 (DIN)
unnamed: LED9.2 (DOUT), LED10.3 (DIN)
unnamed: LED10.2 (DOUT), LED11.3 (DIN)
unnamed: LED11.2 (DOUT), LED12.3 (DIN)
unnamed: LED12.2 (DOUT), LED13.3 (DIN)
unnamed: LED13.2 (DOUT), LED14.3 (DIN)
unnamed: LED14.2 (DOUT), LED29.3 (DIN)
unnamed: LED15.3 (DIN), LED16.2 (DOUT)
unnamed: LED15.2 (DOUT), LED30.3 (DIN)
unnamed: LED16.3 (DIN), LED17.2 (DOUT)
unnamed: LED17.3 (DIN), LED18.2 (DOUT)
unnamed: LED18.3 (DIN), LED19.2 (DOUT)
unnamed: LED19.3 (DIN), LED20.2 (DOUT)
unnamed: LED20.3 (DIN), LED21.2 (DOUT)
unnamed: LED21.3 (DIN), LED22.2 (DOUT)
unnamed: LED22.3 (DIN), LED23.2 (DOUT)
unnamed: LED23.3 (DIN), LED24.2 (DOUT)
unnamed: LED24.3 (DIN), LED25.2 (DOUT)
unnamed: LED25.3 (DIN), LED26.2 (DOUT)
unnamed: LED26.3 (DIN), LED27.2 (DOUT)
unnamed: LED27.3 (DIN), LED28.2 (DOUT)
unnamed: LED28.3 (DIN), LED29.2 (DOUT)
unnamed: LED30.2 (DOUT), LED31.3 (DIN)
unnamed: LED31.2 (DOUT), LED32.3 (DIN)
unnamed: LED32.2 (DOUT), LED33.3 (DIN)
unnamed: LED33.2 (DOUT), LED34.3 (DIN)
unnamed: LED34.2 (DOUT), LED35.3 (DIN)
unnamed: LED35.2 (DOUT), LED36.3 (DIN)
unnamed: LED36.2 (DOUT), LED37.3 (DIN)
unnamed: LED37.2 (DOUT), LED38.3 (DIN)
unnamed: LED38.2 (DOUT), LED39.3 (DIN)
unnamed: LED39.2 (DOUT), LED40.3 (DIN)
unnamed: LED40.2 (DOUT), LED41.3 (DIN)
unnamed: LED41.2 (DOUT), LED42.3 (DIN)
unnamed: LED42.2 (DOUT), LED43.3 (DIN)
unnamed: LED43.2 (DOUT), LED44.3 (DIN)
unnamed: LED44.2 (DOUT), LED58.3 (DIN)
unnamed: LED45.3 (DIN), LED46.2 (DOUT)
unnamed: LED45.2 (DOUT), LED59.3 (DIN)
unnamed: LED46.3 (DIN), LED47.2 (DOUT)
unnamed: LED47.3 (DIN), LED48.2 (DOUT)
unnamed: LED48.3 (DIN), LED49.2 (DOUT)
unnamed: LED49.3 (DIN), LED50.2 (DOUT)
unnamed: LED50.3 (DIN), LED51.2 (DOUT)
unnamed: LED51.3 (DIN), LED52.2 (DOUT)
unnamed: LED52.3 (DIN), LED53.2 (DOUT)
unnamed: LED53.3 (DIN), LED54.2 (DOUT)
unnamed: LED54.3 (DIN), LED55.2 (DOUT)
unnamed: LED55.3 (DIN), LED56.2 (DOUT)
unnamed: LED56.3 (DIN), LED57.2 (DOUT)
unnamed: LED57.3 (DIN), LED58.2 (DOUT)
unnamed: LED59.2 (DOUT), LED60.3 (DIN)
unnamed: LED60.2 (DOUT), LED61.3 (DIN)
unnamed: LED61.2 (DOUT), LED62.3 (DIN)
unnamed: LED62.2 (DOUT), LED63.3 (DIN)
unnamed: LED63.2 (DOUT), LED64.3 (DIN)
unnamed: LED64.2 (DOUT), LED65.3 (DIN)
unnamed: LED65.2 (DOUT), LED66.3 (DIN)
unnamed: LED66.2 (DOUT), LED67.3 (DIN)
unnamed: LED67.2 (DOUT), LED68.3 (DIN)
unnamed: LED68.2 (DOUT), LED69.3 (DIN)
unnamed: LED69.2 (DOUT), LED70.3 (DIN)
unnamed: LED70.2 (DOUT), LED71.3 (DIN)
unnamed: LED71.2 (DOUT), LED81.3 (DIN)
unnamed: LED72.3 (DIN), LED73.2 (DOUT)
unnamed: LED73.3 (DIN), LED74.2 (DOUT)
unnamed: LED74.3 (DIN), LED75.2 (DOUT)
unnamed: LED75.3 (DIN), LED76.2 (DOUT)
unnamed: LED76.3 (DIN), LED77.2 (DOUT)
unnamed: LED77.3 (DIN), LED78.2 (DOUT)
unnamed: LED78.3 (DIN), LED79.2 (DOUT)
unnamed: LED79.3 (DIN), LED80.2 (DOUT)
unnamed: LED80.3 (DIN), LED81.2 (DOUT)
unnamed: R16.2, U6.34 (IO5)
unnamed: C31.1, U6.26 (VDD_SDIO)
unnamed: C28.2, U8.6 (V3_{OUT})
RTS: Q7.5 (B2), U8.13 (~RTS)
STATUS: AMB10.2 (DOUT), GLO1.3 (DIN)
VBUS: F1.1, JST1.1, VC1.1
